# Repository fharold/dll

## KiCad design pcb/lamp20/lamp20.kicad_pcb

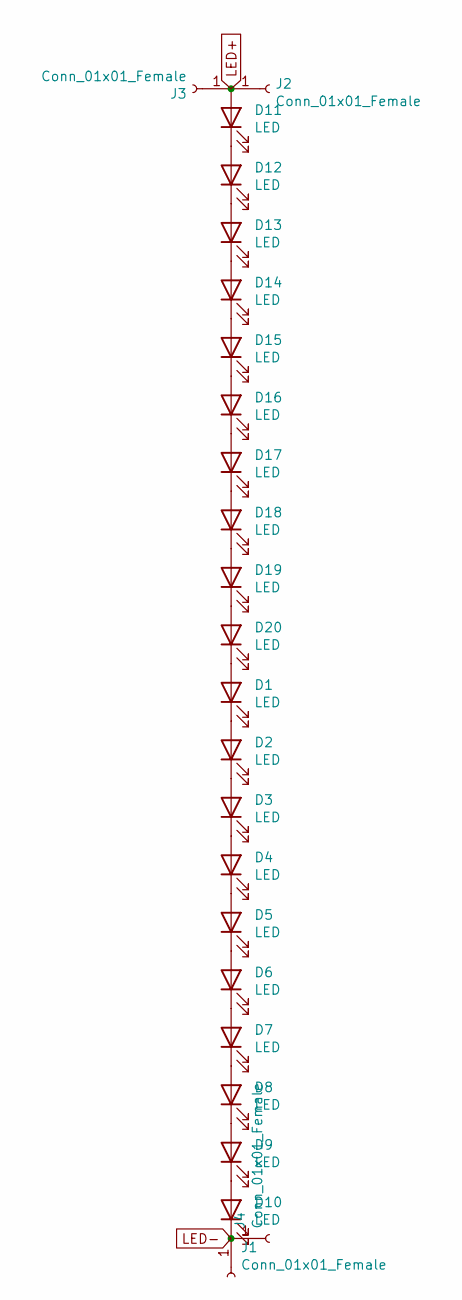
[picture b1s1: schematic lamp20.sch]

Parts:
D1, D2, D3, D4, D5, D6, D7, D8, D9, D10, D11, D12, D13, D14, D15, D16, D17, D18, D19, D20: LED; LED_PLCC_2835_Handsoldering
J1, J2, J3, J4: Conn_01x01_Female; SolderWirePad_1x01_SMD_1x2mm

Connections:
LED+: D11.2 (A), J2.1, J3.1
LED-: D10.1 (K), J1.1, J4.1
unnamed: D1.1 (K), D2.2 (A)
unnamed: D1.2 (A), D20.1 (K)
unnamed: D2.1 (K), D3.2 (A)
unnamed: D3.1 (K), D4.2 (A)
unnamed: D4.1 (K), D5.2 (A)
unnamed: D5.1 (K), D6.2 (A)
unnamed: D6.1 (K), D7.2 (A)
unnamed: D7.1 (K), D8.2 (A)
unnamed: D8.1 (K), D9.2 (A)
unnamed: D9.1 (K), D10.2 (A)
unnamed: D11.1 (K), D12.2 (A)
unnamed: D12.1 (K), D13.2 (A)
unnamed: D13.1 (K), D14.2 (A)
unnamed: D14.1 (K), D15.2 (A)
unnamed: D15.1 (K), D16.2 (A)
unnamed: D16.1 (K), D17.2 (A)
unnamed: D17.1 (K), D18.2 (A)
unnamed: D18.1 (K), D19.2 (A)
unnamed: D19.1 (K), D20.2 (A)

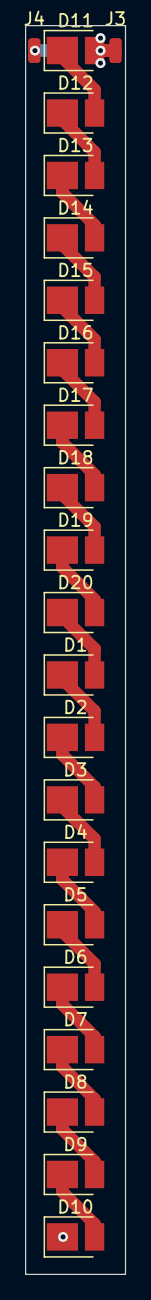
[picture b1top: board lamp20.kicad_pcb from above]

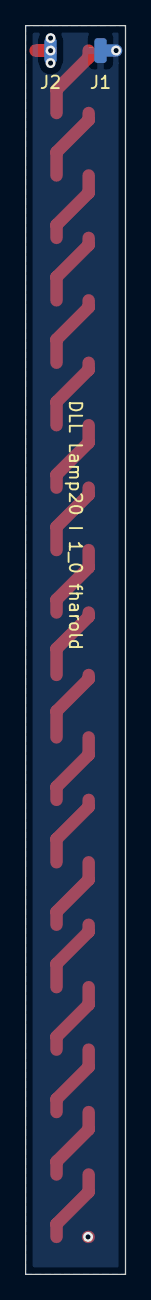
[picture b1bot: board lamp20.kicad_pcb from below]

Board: 2 copper layers, 8.0 x 100.0 mm, 24 parts (2 on the bottom side), 21 nets.

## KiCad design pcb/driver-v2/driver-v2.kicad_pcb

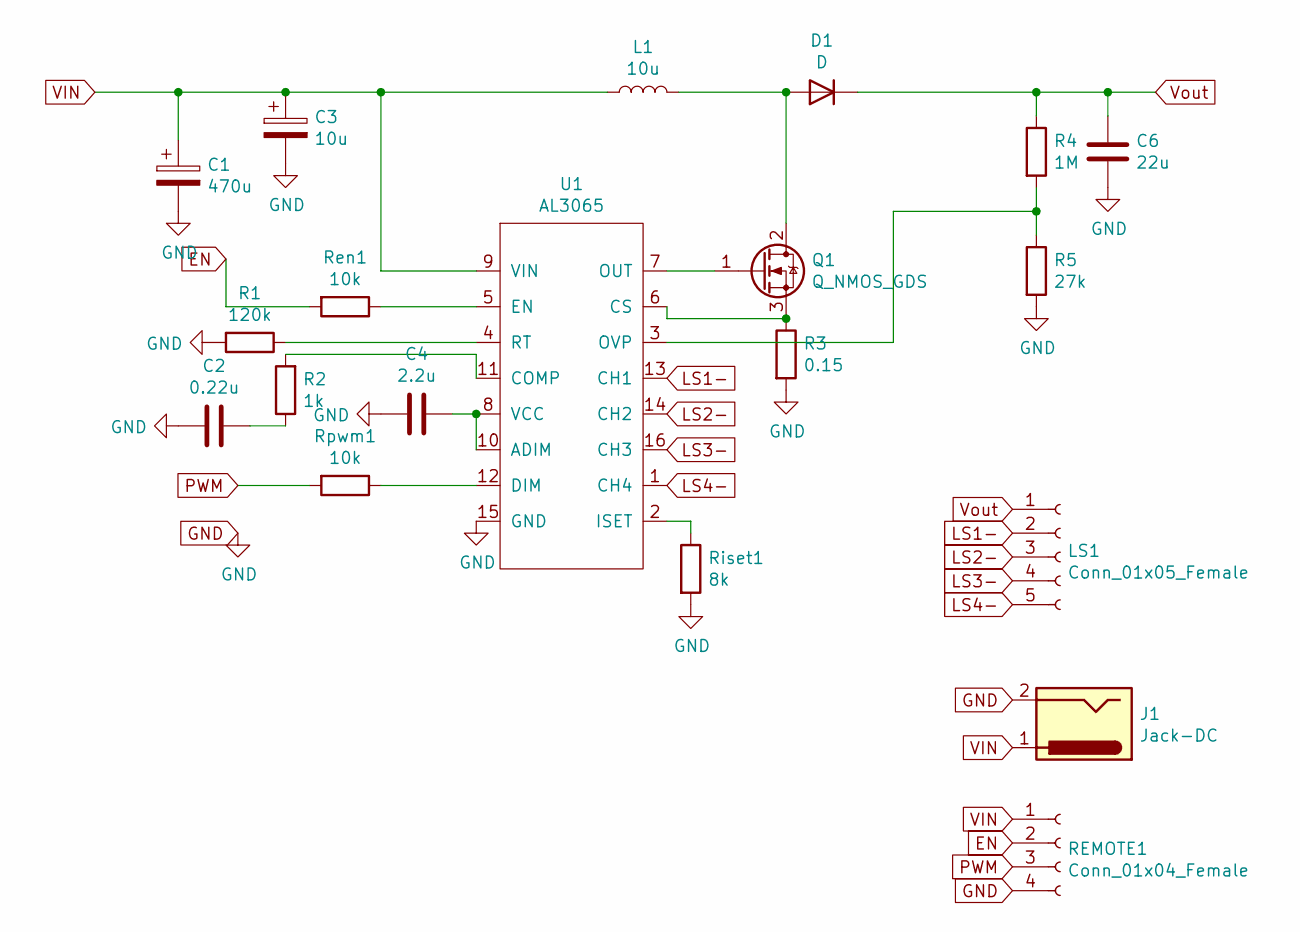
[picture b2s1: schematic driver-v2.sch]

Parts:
C1: 470u; CP_Radial_D10.0mm_P5.00mm
C2: 0.22u; C_0805_2012Metric_Pad1.15x1.40mm_HandSolder
C3: 10u; CP_Elec_4x5.4
C4: 2.2u; C_0805_2012Metric_Pad1.15x1.40mm_HandSolder
C6: 22u; C_Elec_8x10.2
D1: D; D_SMA_Handsoldering
J1: Jack-DC; BarrelJack_Wuerth_6941xx301002
L1: 10u; L_Bourns-SRU1028_10.0x10.0mm
LS1: Conn_01x05_Female; PinSocket_1x05_P2.54mm_Horizontal
Q1: Q_NMOS_GDS; TO-252-2
R1: 120k; R_0805_2012Metric_Pad1.15x1.40mm_HandSolder
R2: 1k; R_0805_2012Metric_Pad1.15x1.40mm_HandSolder
R3: 0.15; R_2512_6332Metric_Pad1.52x3.35mm_HandSolder
R4: 1M; R_0805_2012Metric_Pad1.15x1.40mm_HandSolder
R5: 27k; R_0805_2012Metric_Pad1.15x1.40mm_HandSolder
REMOTE1: Conn_01x04_Female; PinSocket_1x04_P2.54mm_Horizontal
Ren1: 10k; R_0805_2012Metric_Pad1.15x1.40mm_HandSolder
Riset1: 8k; R_0805_2012Metric_Pad1.15x1.40mm_HandSolder
Rpwm1: 10k; R_0805_2012Metric_Pad1.15x1.40mm_HandSolder
U1: AL3065; SO-16_5.3x10.2mm_P1.27mm

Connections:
EN: REMOTE1.2, Ren1.2
GND: C1.2, C2.2, C3.2, C4.2, C6.2, J1.2, R1.2, R3.2, R5.2, REMOTE1.4, Riset1.2, U1.15 (GND)
LS1-: LS1.2, U1.13 (CH1)
LS2-: LS1.3, U1.14 (CH2)
LS3-: LS1.4, U1.16 (CH3)
LS4-: LS1.5, U1.1 (CH4)
unnamed: C2.1, R2.1
unnamed: C4.1, U1.8 (VCC), U1.10 (ADIM)
unnamed: D1.2 (A), L1.2, Q1.2 (D)
unnamed: Q1.1 (G), U1.7 (OUT)
unnamed: Q1.3 (S), R3.1, U1.6 (CS)
unnamed: R1.1, U1.4 (RT)
unnamed: R2.2, U1.11 (COMP)
unnamed: R4.2, R5.1, U1.3 (OVP)
unnamed: Ren1.1, U1.5 (EN)
unnamed: Riset1.1, U1.2 (ISET)
unnamed: Rpwm1.1, U1.12 (DIM)
PWM: REMOTE1.3, Rpwm1.2
VIN: C1.1, C3.1, J1.1, L1.1, REMOTE1.1, U1.9 (VIN)
Vout: C6.1, D1.1 (K), LS1.1, R4.1

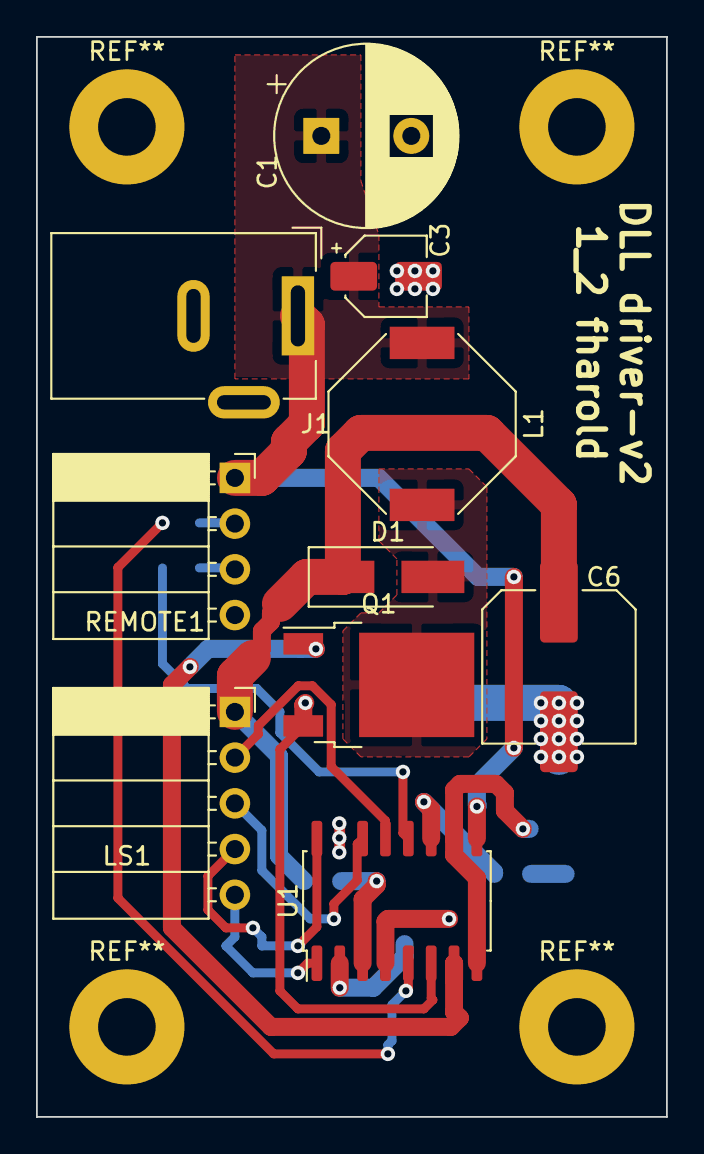
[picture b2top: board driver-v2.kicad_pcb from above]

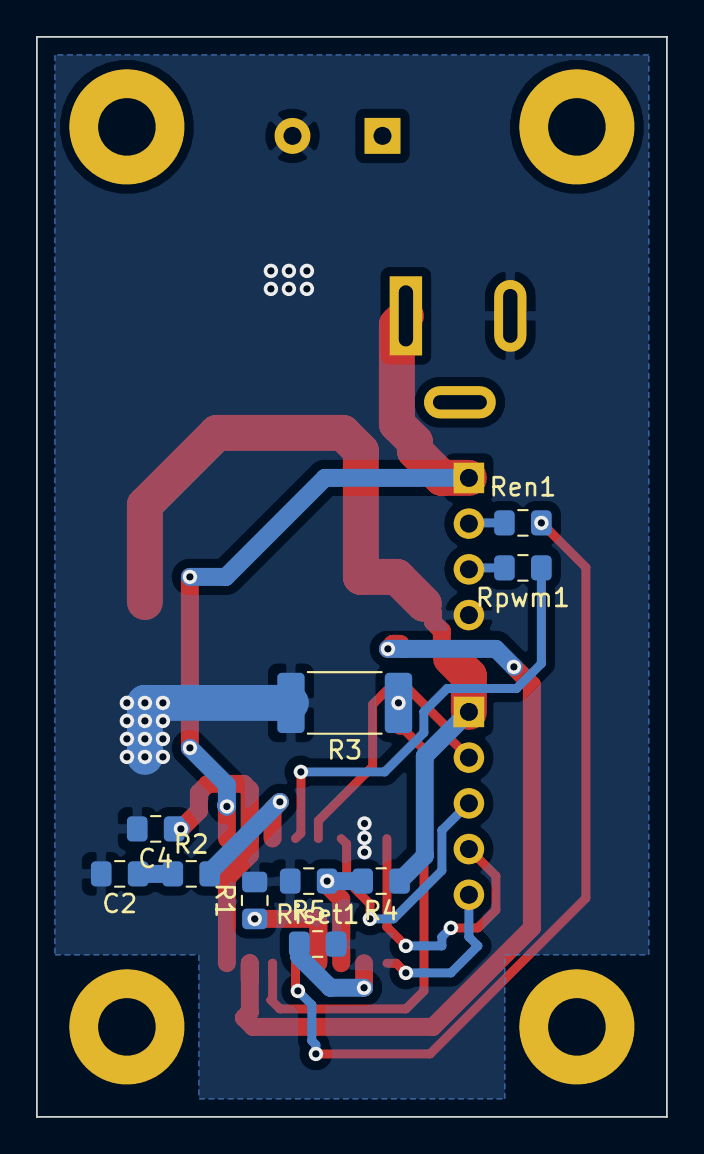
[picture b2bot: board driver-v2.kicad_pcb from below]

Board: 2 copper layers, 35.0 x 60.0 mm, 20 parts (10 on the bottom side), 20 nets.

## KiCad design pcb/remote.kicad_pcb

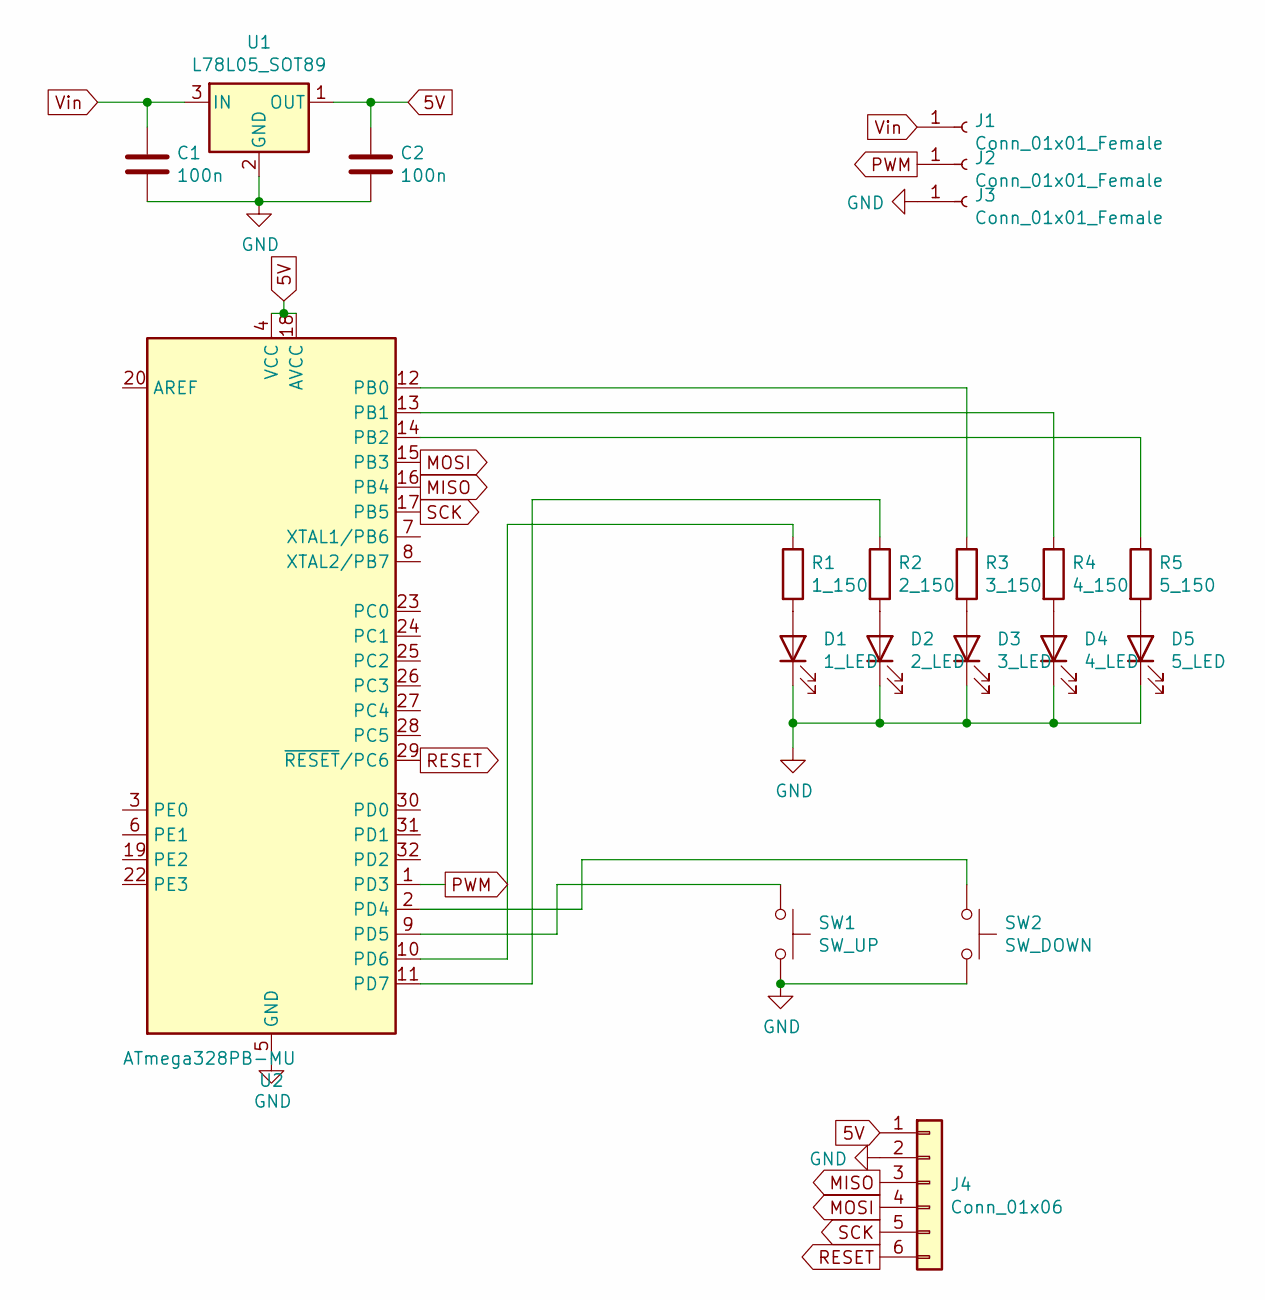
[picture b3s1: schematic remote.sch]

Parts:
C1, C2: 100n; C_1206_3216Metric_Pad1.42x1.75mm_HandSolder
D1: 1_LED; LED_0603_1608Metric_Pad1.05x0.95mm_HandSolder
D2: 2_LED; LED_0603_1608Metric_Pad1.05x0.95mm_HandSolder
D3: 3_LED; LED_0603_1608Metric_Pad1.05x0.95mm_HandSolder
D4: 4_LED; LED_0603_1608Metric_Pad1.05x0.95mm_HandSolder
D5: 5_LED; LED_0603_1608Metric_Pad1.05x0.95mm_HandSolder
J1, J2, J3: Conn_01x01_Female; TestPoint_Pad_1.5x1.5mm
J4: Conn_01x06; Hirose_FH12-6S-0.5SH_1x06-1MP_P0.50mm_Horizontal
R1: 1_150; R_0603_1608Metric_Pad1.05x0.95mm_HandSolder
R2: 2_150; R_0603_1608Metric_Pad1.05x0.95mm_HandSolder
R3: 3_150; R_0603_1608Metric_Pad1.05x0.95mm_HandSolder
R4: 4_150; R_0603_1608Metric_Pad1.05x0.95mm_HandSolder
R5: 5_150; R_0603_1608Metric_Pad1.05x0.95mm_HandSolder
SW1: SW_UP; SW_SPST_EVQP2
SW2: SW_DOWN; SW_SPST_EVQP2
U1: L78L05_SOT89; SOT-89-3
U2: ATmega328PB-MU; QFN-32-1EP_5x5mm_P0.5mm_EP3.1x3.1mm

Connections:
5V: C2.1, J4.1, U1.1 (OUT), U2.4 (VCC), U2.18 (AVCC)
GND: C1.2, C2.2, D1.1 (K), D2.1 (K), D3.1 (K), D4.1 (K), D5.1 (K), J3.1, J4.2, SW1.2, SW2.2, U1.2 (GND), U2.5 (GND), U2.21 (GND), U2.33 (GND)
MISO: J4.3, U2.16 (PB4)
MOSI: J4.4, U2.15 (PB3)
unnamed: D1.2 (A), R1.2
unnamed: D2.2 (A), R2.2
unnamed: D3.2 (A), R3.2
unnamed: D4.2 (A), R4.2
unnamed: D5.2 (A), R5.2
unnamed: R1.1, U2.10 (PD6)
unnamed: R2.1, U2.11 (PD7)
unnamed: R3.1, U2.12 (PB0)
unnamed: R4.1, U2.13 (PB1)
unnamed: R5.1, U2.14 (PB2)
unnamed: SW1.1, U2.9 (PD5)
unnamed: SW2.1, U2.2 (PD4)
PWM: J2.1, U2.1 (PD3)
RESET: J4.6, U2.29 (~RESET~/PC6)
SCK: J4.5, U2.17 (PB5)
Vin: C1.1, J1.1, U1.3 (IN)

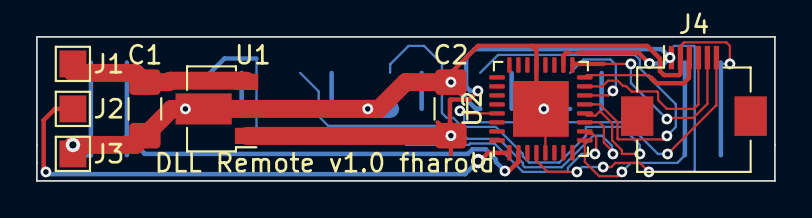
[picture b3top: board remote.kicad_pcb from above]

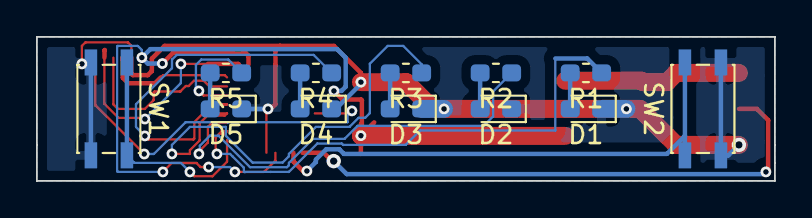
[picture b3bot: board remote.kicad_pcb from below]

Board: 2 copper layers, 41.0 x 8.0 mm, 20 parts (12 on the bottom side), 20 nets.

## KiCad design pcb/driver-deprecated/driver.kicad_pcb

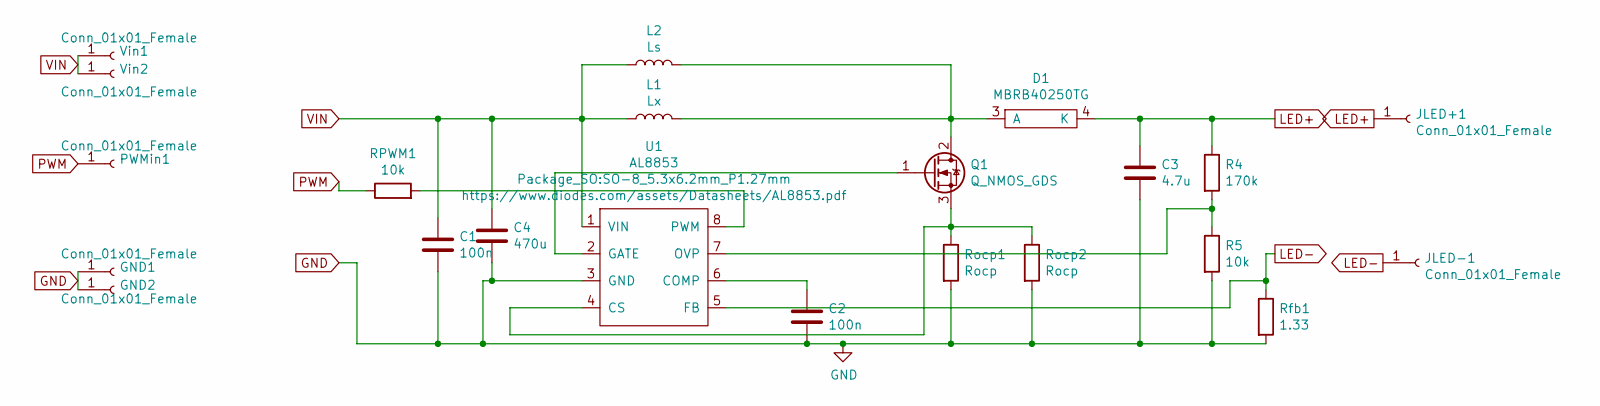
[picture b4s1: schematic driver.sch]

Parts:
C1, C2: 100n; C_0603_1608Metric_Pad1.05x0.95mm_HandSolder
C3: 4.7u; C_Radial_D10.0mm_H16.0mm_P5.00mm
C4: 470u; C_Elec_10x10.2
D1: MBRB40250TG; TO-263-3_TabPin4
GND1: Conn_01x01_Female; SolderWirePad_1x01_SMD_5x10mm
GND2: Conn_01x01_Female; SolderWirePad_1x01_SMD_1x2mm
JLED+1: Conn_01x01_Female; SolderWirePad_1x01_SMD_1x2mm
JLED-1: Conn_01x01_Female; SolderWirePad_1x01_SMD_1x2mm
L1: Lx; L_17x17_H7
L2: Ls; L_12x12mm_H8mm
PWMin1: Conn_01x01_Female; SolderWirePad_1x01_SMD_1x2mm
Q1: Q_NMOS_GDS; SOT-223-3_TabPin2
R4: 170k; R_0603_1608Metric_Pad1.05x0.95mm_HandSolder
R5: 10k; R_0603_1608Metric_Pad1.05x0.95mm_HandSolder
RPWM1: 10k; R_0603_1608Metric_Pad1.05x0.95mm_HandSolder
Rfb1: 1.33; R_0805_2012Metric_Pad1.15x1.40mm_HandSolder
Rocp1, Rocp2: Rocp; R_2512_6332Metric_Pad1.52x3.35mm_HandSolder
U1: AL8853; SO-8_5.3x6.2mm_P1.27mm
Vin1: Conn_01x01_Female; SolderWirePad_1x01_SMD_5x10mm
Vin2: Conn_01x01_Female; SolderWirePad_1x01_SMD_1x2mm

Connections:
GND: C1.2, C2.2, C3.2, C4.2, GND1.1, GND2.1, R5.2, Rfb1.2, Rocp1.2, Rocp2.2, U1.3 (GND)
LED+: C3.1, D1.4 (K), JLED+1.1, R4.1
LED-: JLED-1.1, Rfb1.1, U1.5 (FB)
unnamed: C2.1, U1.6 (COMP)
unnamed: D1.3 (A), L1.2, L2.2, Q1.2 (D)
unnamed: Q1.1 (G), U1.2 (GATE)
unnamed: Q1.3 (S), Rocp1.1, Rocp2.1, U1.4 (CS)
unnamed: R4.2, R5.1, U1.7 (OVP)
unnamed: RPWM1.2, U1.8 (PWM)
PWM: PWMin1.1, RPWM1.1
VIN: C1.1, C4.1, L1.1, L2.1, U1.1 (VIN), Vin1.1, Vin2.1

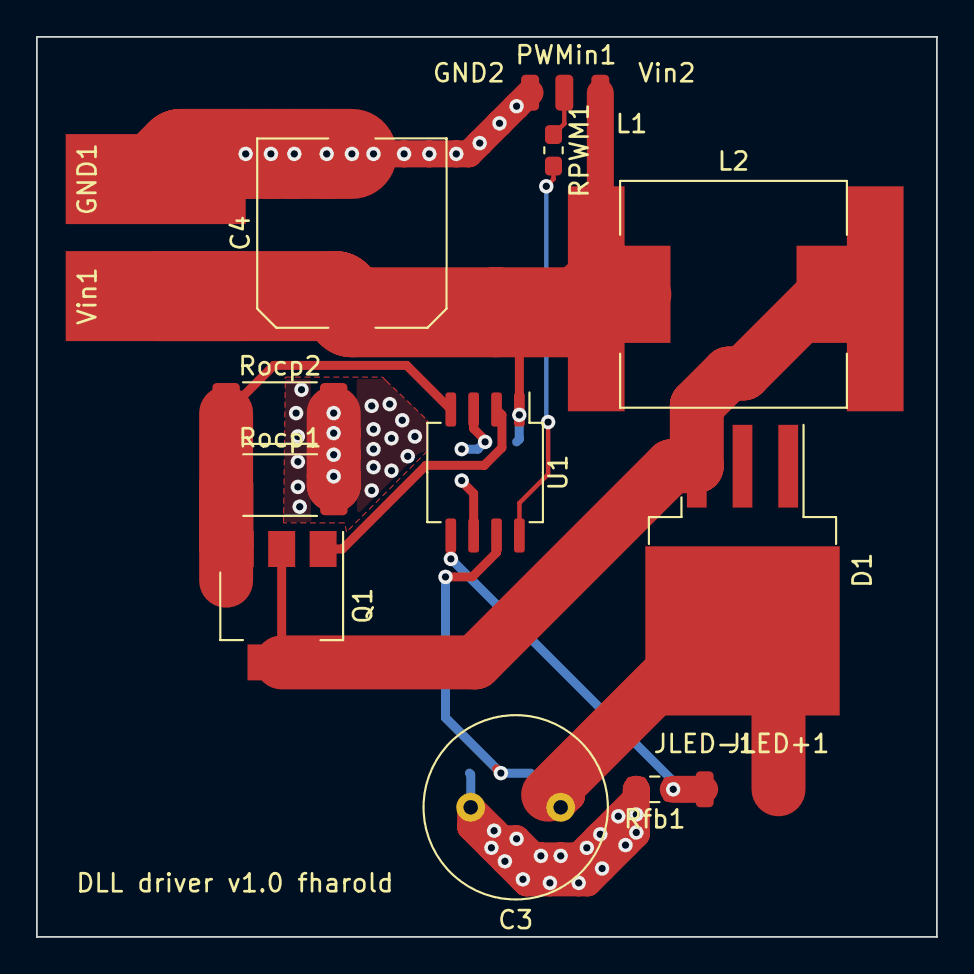
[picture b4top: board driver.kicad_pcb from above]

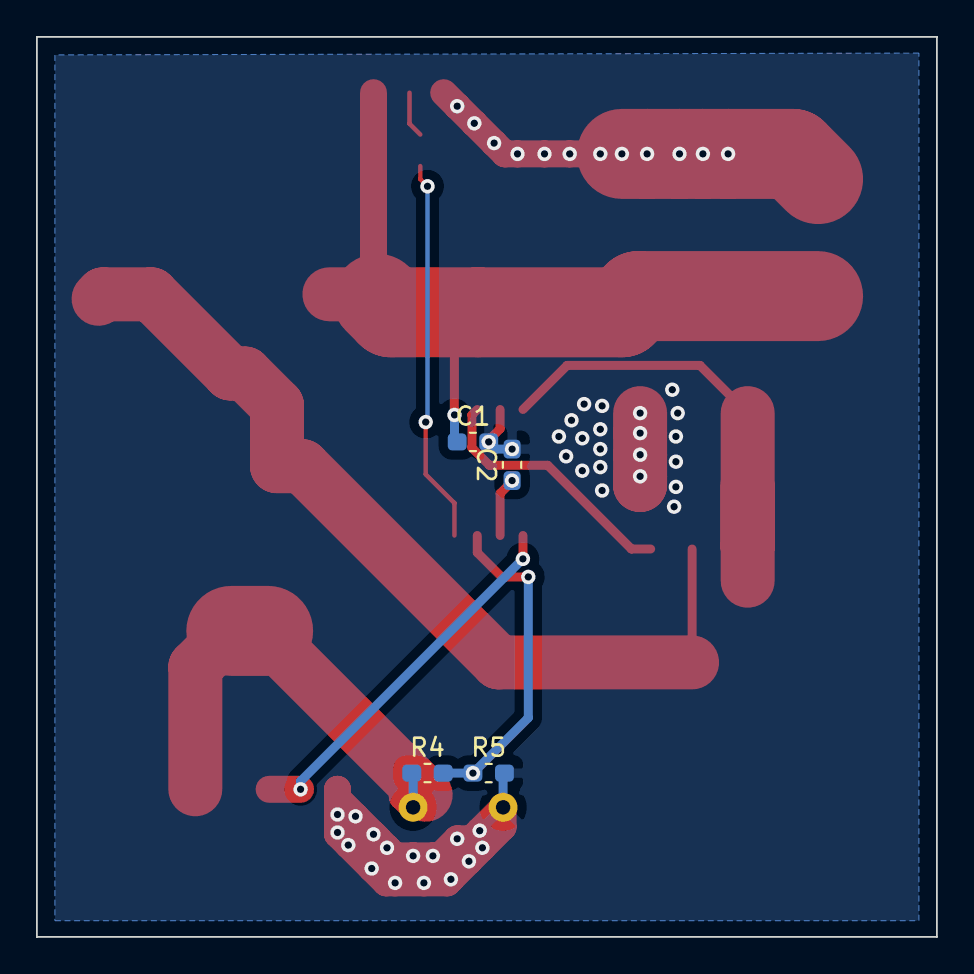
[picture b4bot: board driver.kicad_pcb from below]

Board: 2 copper layers, 50.0 x 50.0 mm, 22 parts (4 on the bottom side), 11 nets.

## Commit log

2020-12-21 initial commit with remote files
2021-01-01 pcbs in progress
2021-01-05 added firmware and updated driver pcnb
